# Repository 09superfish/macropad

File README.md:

# Macropad

A custom 5×5 mechanical macropad built around the ATmega32U4-MU microcontroller. This is a two-person hobby project — one handles the PCB design, the other handles the firmware.

> ⚠️ **Status: PCB designed — not yet built.** This project is still in the hardware design phase.

---

## Overview

| Property | Details |
|----------|---------|
| Layout | 5×5 (25 keys) |
| Microcontroller | ATmega32U4-MU |
| PCB Tool | KiCad |
| Firmware | Custom (ATmega32U4) |
| Status | PCB designed, not built |

---

## Project Structure

```
macropad/
├── KiCad/          # Schematic and PCB layout files
├── firmware/       # Firmware source (ATmega32U4)
└── README.md
```

---

## Pin Mapping

The 5×5 key matrix uses the following pin assignment:

| Function | Pins |
|----------|------|
| Rows (output) | PB0, PB1, PB2, PB3, PB4 |
| Columns (input, pull-up) | PF0, PF1, PF2, PF3, PB5 |

---

## Hardware

- **MCU:** ATmega32U4-MU (QFN-44 package)
- **PCB:** Designed in KiCad
- **Interface:** USB (native USB support on the 32U4)
- **Key matrix:** 5×5 with diodes per key to prevent ghosting

---

## Firmware

Firmware is written for the ATmega32U4 and maintained separately. The firmware handles:

- Matrix scanning
- USB HID communication
- Key mapping / layers

---

## Team

| Role | Person |
|------|--------|
| PCB Design | [@09superfish](https://github.com/09superfish) |
| Firmware | TBD (friend's GitHub handle) |

---

## Branches

| Branch | Description |
|--------|-------------|
| `main` | outdated design |
| `routing-re-design` | Current PCB routing rework |

---

## License

This project is licensed under the [MIT License](LICENSE). Feel free to use it as a reference for your own macropad builds.

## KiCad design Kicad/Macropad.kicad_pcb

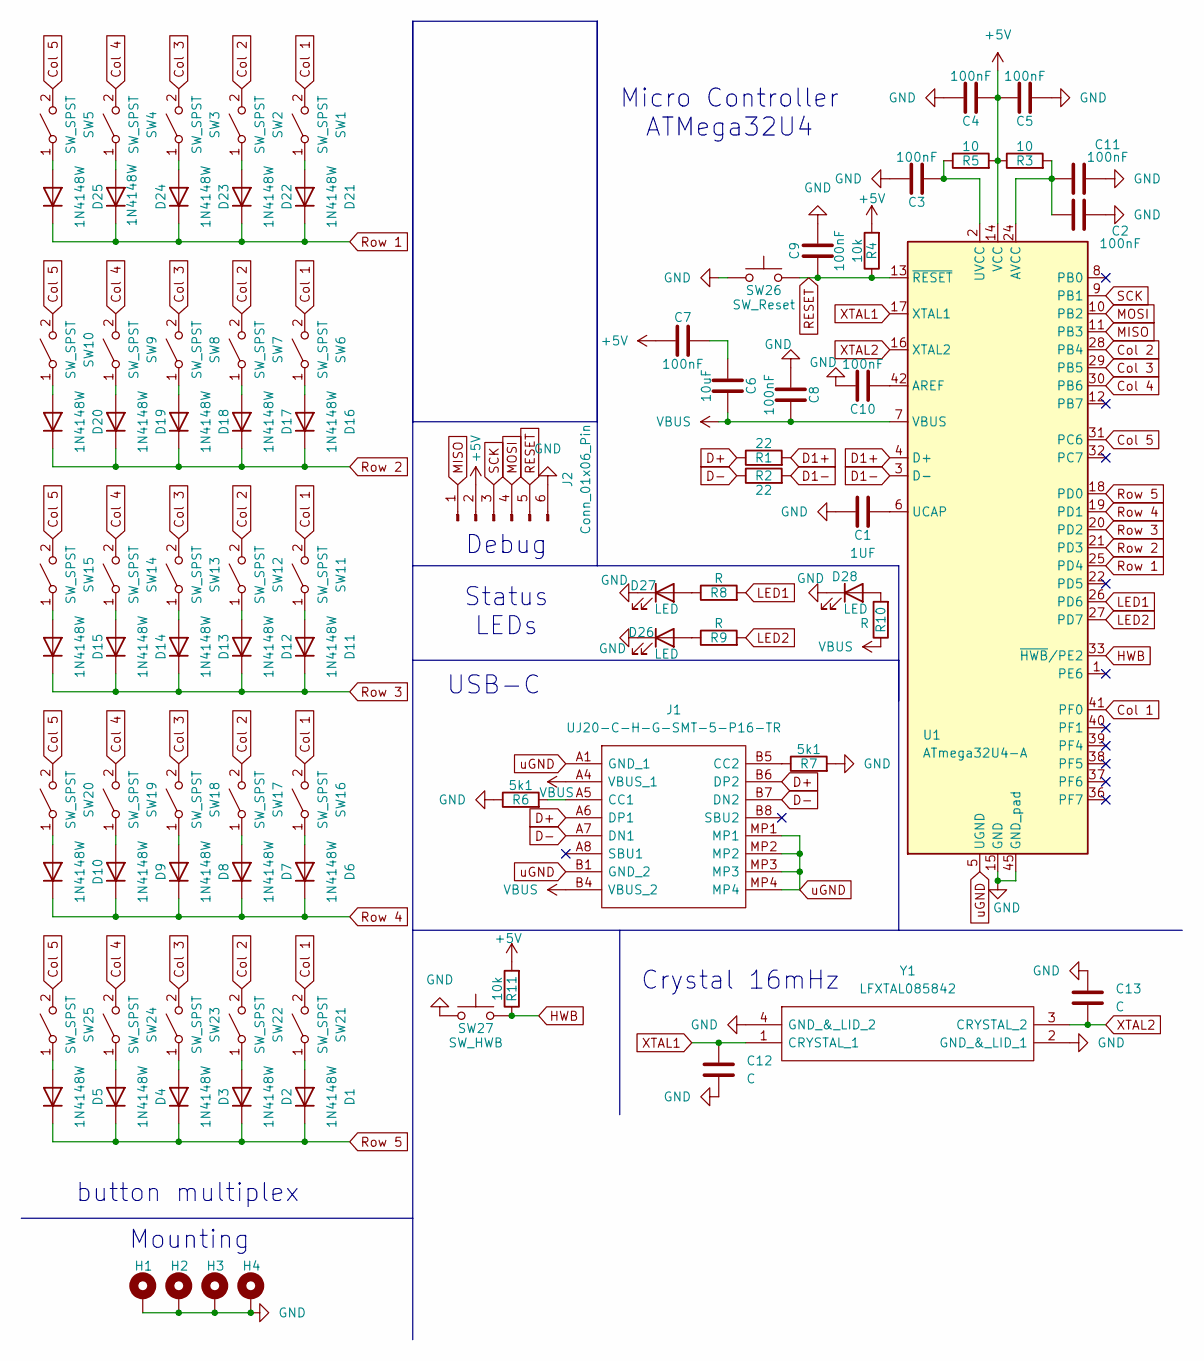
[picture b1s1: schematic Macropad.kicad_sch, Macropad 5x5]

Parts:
C1: 1UF; C_0603_1608Metric
C2, C3, C4, C5, C7, C8, C9, C10, C11: 100nF; C_0603_1608Metric
C6: 10uF; C_0603_1608Metric
C12, C13: C; C_0603_1608Metric
D1, D2, D3, D4, D5, D6, D7, D8, D9, D10, D11, D12, D13, D14, D15, D16, D17, D18, D19, D20, D21, D22, D23, D24, D25: 1N4148W; D_SOD-123
D26, D27, D28: LED; LED_0603_1608Metric
H1, H2, H3, H4: MountingHole_Pad; MountingHole_3.2mm_M3_Pad
J1: UJ20-C-H-G-SMT-5-P16-TR; UJ20CHGSMT5P16TR; Mouser Part Number 179-UJ20CHGSMT5P16TR
J2: Conn_01x06_Pin; PinHeader_2x03_P2.54mm_Vertical
R1, R2: 22; R_0603_1608Metric
R3, R5: 10; R_0603_1608Metric
R4, R11: 10k; R_0603_1608Metric
R6, R7: 5k1; R_0603_1608Metric
R8, R9, R10: R; R_0603_1608Metric
SW1, SW2, SW3, SW4, SW5, SW6, SW7, SW8, SW9, SW10, SW11, SW12, SW13, SW14, SW15, SW16, SW17, SW18, SW19, SW20, SW21, SW22, SW23, SW24, SW25: SW_SPST; SW_Cherry_MX_1.00u_PCB
SW26: SW_Reset; SW_Push_1P1T_NO_CK_KSC7xxJ
SW27: SW_HWB; SW_Push_1P1T_NO_CK_KSC7xxJ
U1: ATmega32U4-A; QFN-44-1EP_7x7mm_P0.5mm_EP5.15x5.15mm
Y1: LFXTAL085842; Mouser Part Number 449-LFXTAL085842

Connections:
+5V: C4.1, C5.2, C7.2, J2.2, R3.1, R4.2, R5.2, R11.2, U1.14 (VCC), U1.34 (VCC)
Col 1: SW1.2 (B), SW6.2 (B), SW11.2 (B), SW16.2 (B), SW21.2 (B), U1.41 (PF0)
Col 2: SW2.2 (B), SW7.2 (B), SW12.2 (B), SW17.2 (B), SW22.2 (B), U1.28 (PB4)
Col 3: SW3.2 (B), SW8.2 (B), SW13.2 (B), SW18.2 (B), SW23.2 (B), U1.29 (PB5)
Col 4: SW4.2 (B), SW9.2 (B), SW14.2 (B), SW19.2 (B), SW24.2 (B), U1.30 (PB6)
Col 5: SW5.2 (B), SW10.2 (B), SW15.2 (B), SW20.2 (B), SW25.2 (B), U1.31 (PC6)
D1+: R1.2, U1.4 (D+)
D1-: R2.2, U1.3 (D-)
D+: J1.A6 (DP1), J1.B6 (DP2), R1.1
D-: J1.A7 (DN1), J1.B7 (DN2), R2.1
GND: C1.2, C2.2, C3.2, C4.2, C5.1, C8.1, C9.2, C10.2, C11.2, C12.2, C13.1, D26.1 (K), D27.1 (K), D28.1 (K), H1.1, H2.1, H3.1, H4.1, J2.6, R6.1, R7.2, SW26.1, SW27.1, U1.15 (GND), U1.23 (GND), U1.35 (GND), U1.43 (GND), U1.45 (GND_pad), Y1.2 (GND_&_LID_1), Y1.4 (GND_&_LID_2)
HWB: R11.1, SW27.2, U1.33 (~HWB/PE2)
LED1: R8.2, U1.26 (PD6)
LED2: R9.2, U1.27 (PD7)
MISO: J2.1, U1.11 (PB3)
MOSI: J2.4, U1.10 (PB2)
unnamed: C6.1, C7.1
unnamed: C2.1, C11.1, R3.2, U1.24 (AVCC), U1.44 (AVCC)
unnamed: D1.2 (A), SW21.1 (A)
unnamed: D2.2 (A), SW22.1 (A)
unnamed: D3.2 (A), SW23.1 (A)
unnamed: D4.2 (A), SW24.1 (A)
unnamed: D5.2 (A), SW25.1 (A)
unnamed: D6.2 (A), SW16.1 (A)
unnamed: D7.2 (A), SW17.1 (A)
unnamed: D8.2 (A), SW18.1 (A)
unnamed: D9.2 (A), SW19.1 (A)
unnamed: D10.2 (A), SW20.1 (A)
unnamed: D11.2 (A), SW11.1 (A)
unnamed: D12.2 (A), SW12.1 (A)
unnamed: D13.2 (A), SW13.1 (A)
unnamed: D14.2 (A), SW14.1 (A)
unnamed: D15.2 (A), SW15.1 (A)
unnamed: D16.2 (A), SW6.1 (A)
unnamed: D17.2 (A), SW7.1 (A)
unnamed: D18.2 (A), SW8.1 (A)
unnamed: D19.2 (A), SW9.1 (A)
unnamed: D20.2 (A), SW10.1 (A)
unnamed: D21.2 (A), SW1.1 (A)
unnamed: D22.2 (A), SW2.1 (A)
unnamed: D23.2 (A), SW3.1 (A)
unnamed: D24.2 (A), SW4.1 (A)
unnamed: D25.2 (A), SW5.1 (A)
unnamed: D26.2 (A), R9.1
unnamed: D27.2 (A), R8.1
unnamed: D28.2 (A), R10.2
unnamed: J1.A5 (CC1), R6.2
unnamed: J1.B5 (CC2), R7.1
unnamed: C10.1, U1.42 (AREF)
unnamed: C1.1, U1.6 (UCAP)
unnamed: C3.1, R5.1, U1.2 (UVCC)
RESET: C9.1, J2.5, R4.1, SW26.2, U1.13 (~RESET)
Row 1: D21.1 (K), D22.1 (K), D23.1 (K), D24.1 (K), D25.1 (K), U1.25 (PD4)
Row 2: D16.1 (K), D17.1 (K), D18.1 (K), D19.1 (K), D20.1 (K), U1.21 (PD3)
Row 3: D11.1 (K), D12.1 (K), D13.1 (K), D14.1 (K), D15.1 (K), U1.20 (PD2)
Row 4: D6.1 (K), D7.1 (K), D8.1 (K), D9.1 (K), D10.1 (K), U1.19 (PD1)
Row 5: D1.1 (K), D2.1 (K), D3.1 (K), D4.1 (K), D5.1 (K), U1.18 (PD0)
SCK: J2.3, U1.9 (PB1)
VBUS: C6.2, C8.2, J1.A4 (VBUS_1), J1.B4 (VBUS_2), R10.1, U1.7 (VBUS)
XTAL1: C12.1, U1.17 (XTAL1), Y1.1 (CRYSTAL_1)
XTAL2: C13.2, U1.16 (XTAL2), Y1.3 (CRYSTAL_2)
uGND: J1.A1 (GND_1), J1.B1 (GND_2), J1.MP1, J1.MP2, J1.MP3, J1.MP4, U1.5 (UGND)

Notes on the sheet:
Crystal 16mHz
Status LEDs
Micro Controller ATMega32U4
Mounting
button multiplex
Debug
USB-C

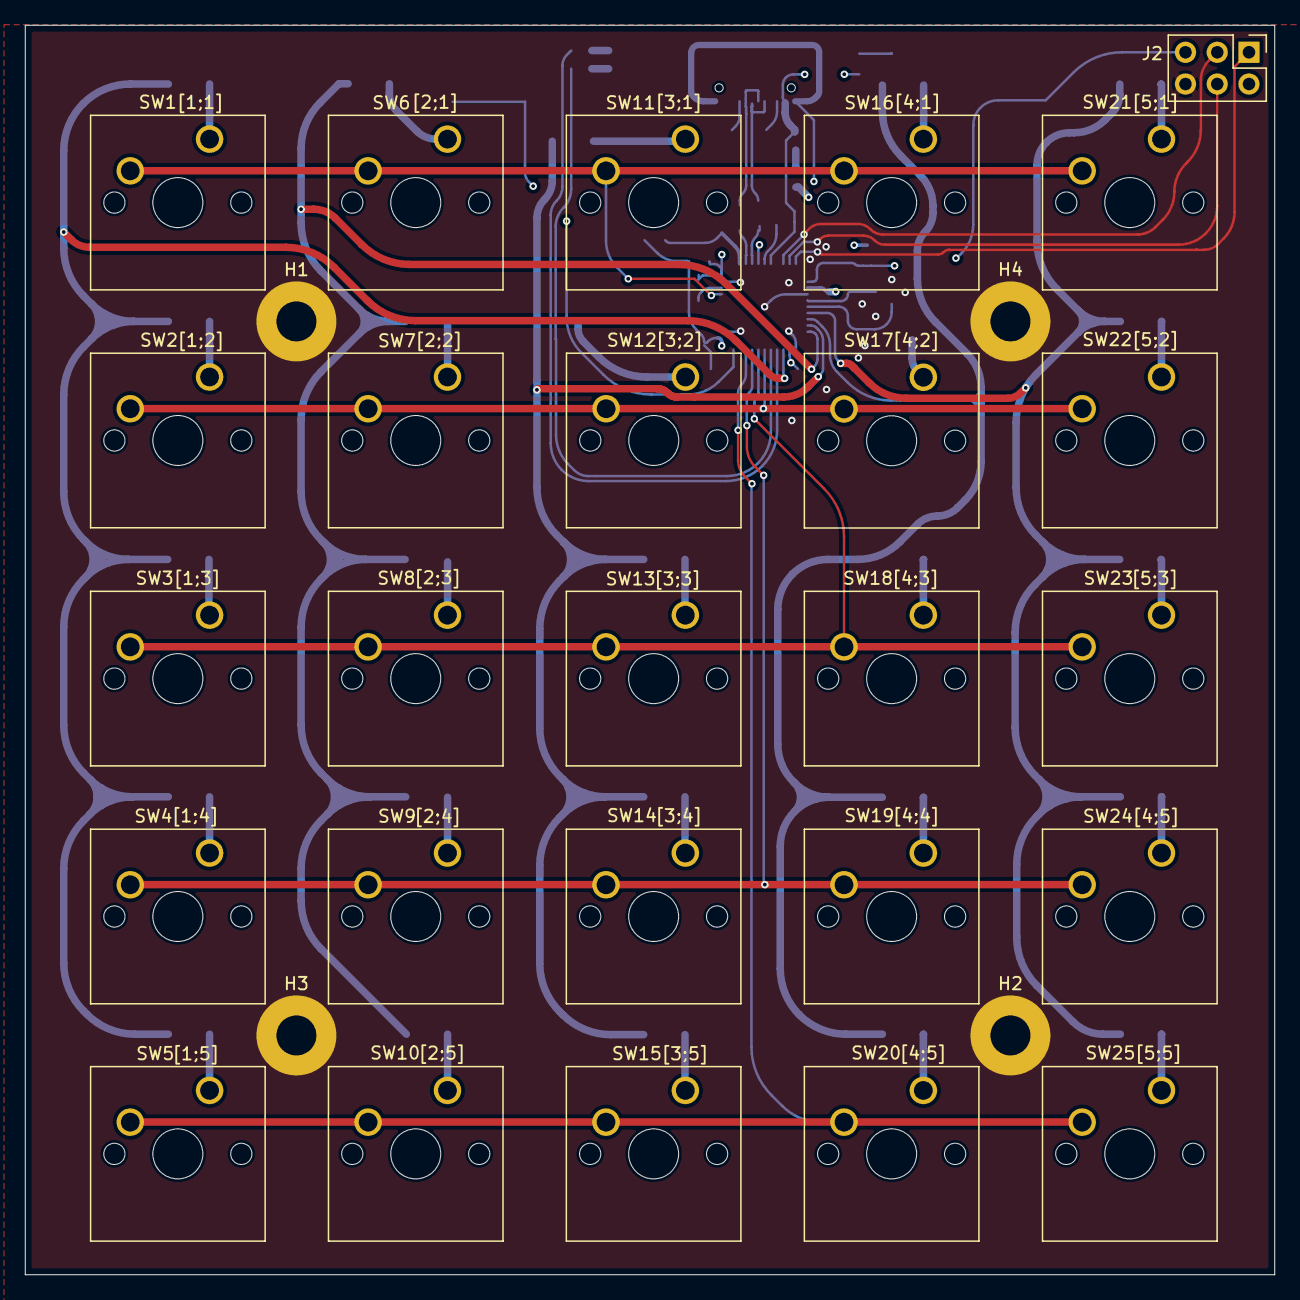
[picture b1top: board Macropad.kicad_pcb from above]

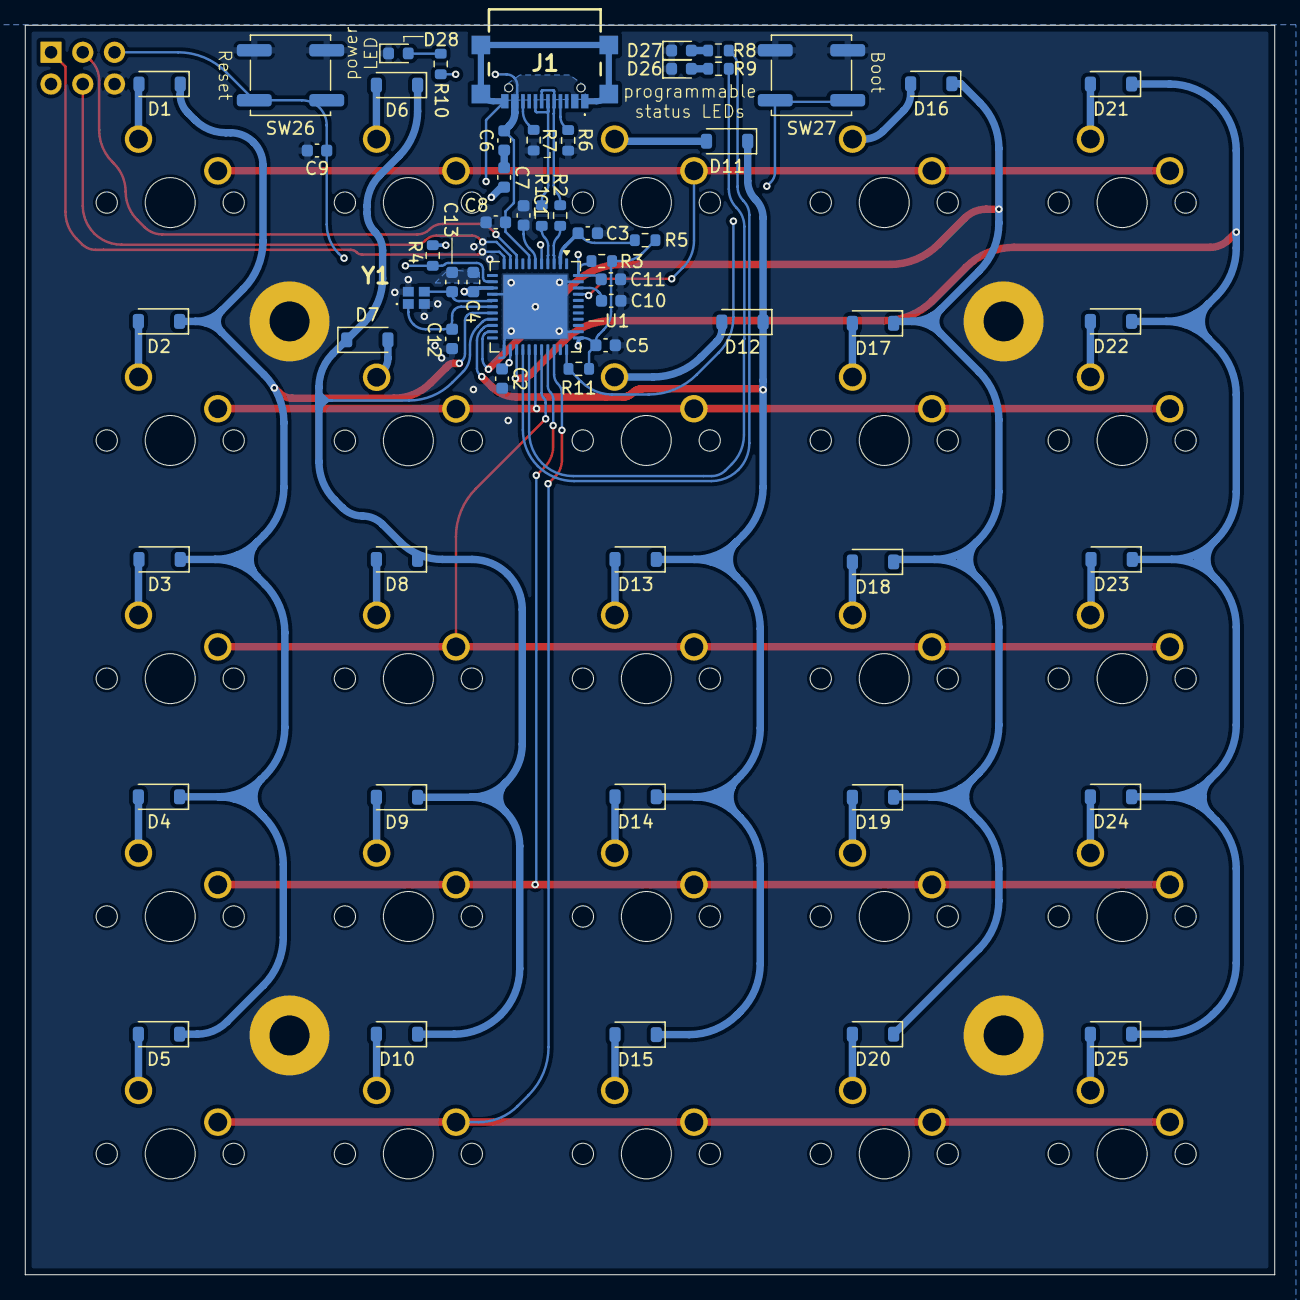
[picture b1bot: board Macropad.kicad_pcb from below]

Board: 4 copper layers, 100.0 x 100.0 mm, 87 parts (57 on the bottom side), 62 nets.

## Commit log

2026-03-12 inital commit, still needs a revision
2026-03-12 moved LED
2026-03-12 reversed LED change
2026-03-13 switched MC to QFN, rerouted board
2026-03-13 Deleted unnecessary files
2026-03-13 restructured files, made a README.md
2026-03-13 moved things around in README.md
2026-03-13 added hardware to the MIT licence
2026-03-13 added debug pins
